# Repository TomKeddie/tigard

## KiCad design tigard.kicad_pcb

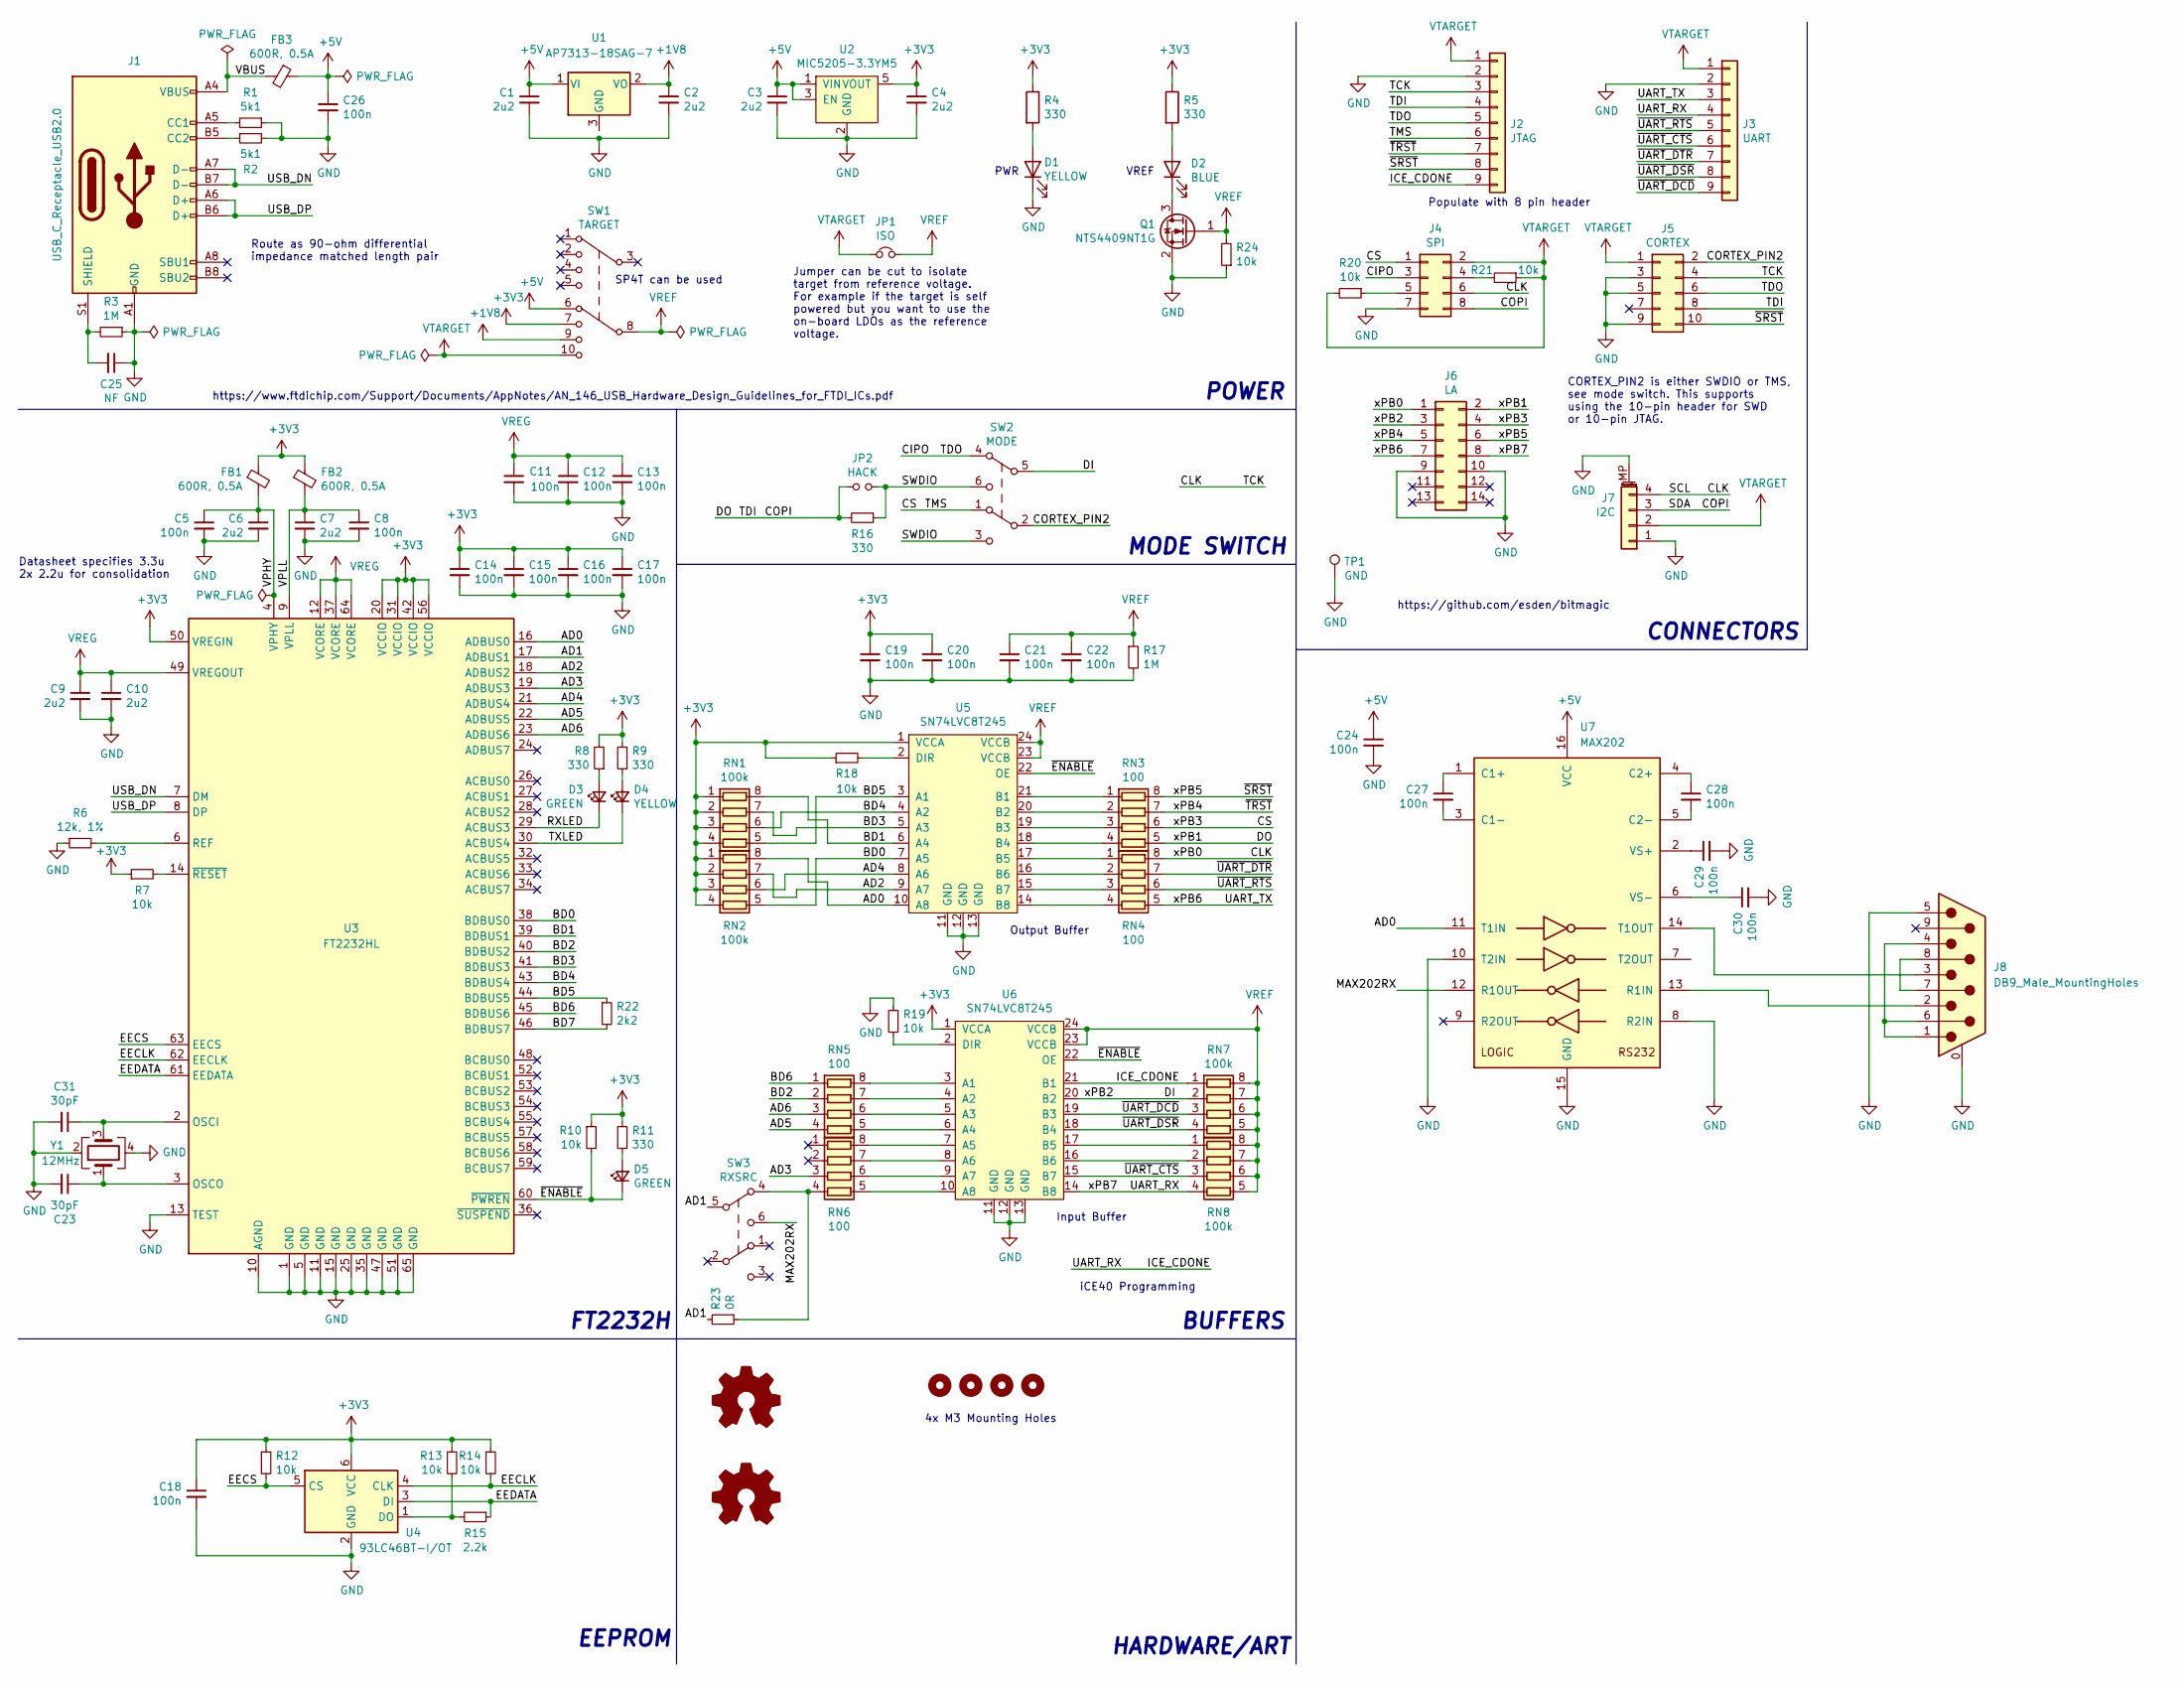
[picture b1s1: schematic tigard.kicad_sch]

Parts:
C1, C2, C3, C4, C6, C7, C9, C10: 2u2; C_0805_2012Metric; LCSC C307419
C5, C8, C11, C12, C13, C14, C15, C16, C17, C18, C19, C20, C21, C22, C24, C26, C27, C28, C29, C30: 100n; C_0805_2012Metric; LCSC C100072
C23, C31: 30pF; C_0805_2012Metric; LCSC C159804
C25: NF; C_0805_2012Metric
D1, D4: YELLOW; LED_0805_2012Metric; LCSC C160477
D2: BLUE; LED_0805_2012Metric; LCSC C157738
D3, D5: GREEN; LED_0805_2012Metric; LCSC C12065
FB1, FB2, FB3: 600R, 0.5A; L_0805_2012Metric; LCSC C76886
H1, H2, H3, H4: MountingHole; MountingHole_3.2mm_M3_ISO7380
J1: USB_C_Receptacle_USB2.0; USB_C_Receptacle_HRO_TYPE-C-31-M-12; LCSC C165948
J2: JTAG; PinHeader_1x09_P2.54mm_Vertical; LCSC C358689
J3: UART; PinHeader_1x09_P2.54mm_Vertical; LCSC C492408
J4: SPI; PinHeader_2x04_P2.54mm_Vertical; LCSC C358693
J5: CORTEX; PinHeader_2x05_P1.27mm_Vertical_SMD; LCSC C448647
J6: LA; PinHeader_2x07_P1.27mm_Vertical_SMD
J7: I2C; JST_SH_SM04B-SRSS-TB_1x04-1MP_P1.00mm_Horizontal; LCSC C160404
J8: DB9_Male_MountingHoles; DSUB-9_Male_Horizontal_P2.77x2.84mm_EdgePinOffset7.70mm_Hou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
JP1: ISO; SolderJumper-2_P1.3mm_Bridged_RoundedPad1.0x1.5mm
JP2: HACK; SolderJumper-2_P1.3mm_Open_RoundedPad1.0x1.5mm
LOGO1: Logo_Open_Hardware_Small; OSHW-Symbol_4.4x4mm_SilkScreen
LOGO2: Logo_Open_Hardware_Small; Tigard_Logo
Q1: NTS4409NT1G; SOT-323_SC-70; LCSC C88711
R1, R2: 5k1; L_0805_2012Metric; LCSC C25941
R3, R17: 1M; L_0805_2012Metric; LCSC C26087
R4, R5, R8, R9, R11, R16: 330; L_0805_2012Metric; LCSC C25104
R6: 12k, 1%; L_0805_2012Metric; LCSC C25752
R7, R10, R12, R13, R14, R18, R19, R20, R21, R24: 10k; L_0805_2012Metric; LCSC C301923
R15: 2.2k; L_0805_2012Metric; LCSC C25879
R22: 2k2; L_0805_2012Metric; LCSC C25933
R23: 0R; L_0805_2012Metric; LCSC C25104
RN1, RN2, RN7, RN8: 100k; R_Array_Convex_4x0603; LCSC C25724
RN3, RN4, RN5, RN6: 100; R_Array_Convex_4x0603; LCSC C48442
SW1: TARGET; SW_ALPS_SSSS224100_DP4T; LCSC C255514
SW2: MODE; SW_CuK_JS202011CQN_DPDT_Straight; LCSC C221663
SW3: RXSRC; SW_CuK_JS202011CQN_DPDT_Straight; LCSC C221663
TP1: GND; TestPoint_Keystone_5000-5004_Miniature; LCSC C238122
U1: AP7313-18SAG-7; SOT-23_RoundRect
U2: MIC5205-3.3YM5; SOT-23-5_RoundRect; LCSC C150742
U3: FT2232HL; LQFP-64_10x10mm_P0.5mm; LCSC C193662
U4: 93LC46BT-I/OT; SOT-23-6_RoundRect; LCSC C190271
U5, U6: SN74LVC8T245; SOIC-24W_7.5x15.4mm_P1.27mm; LCSC C27643
U7: MAX202; SOIC-16_3.9x9.9mm_P1.27mm
Y1: 12MHz; Crystal_SMD_3225-4Pin_3.2x2.5mm_RoundRect; LCSC C9002

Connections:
+1V8: C2.1, SW1.9, U1.2 (VO)
+3V3: C4.1, C14.1, C15.1, C16.1, C17.1, C18.1, C19.1, C20.1, FB1.1, FB2.1, R4.1, R5.1, R7.1, R8.2, R9.2, R10.1, R11.2, R12.1, R13.1, R14.1, R18.1, RN1.1 (R1.1), RN1.2 (R2.1), RN1.3 (R3.1), RN1.4 (R4.1), RN2.1 (R1.1), RN2.2 (R2.1), RN2.3 (R3.1), RN2.4 (R4.1), SW1.7, U2.5 (VOUT), U3.20 (VCCIO), U3.31 (VCCIO), U3.42 (VCCIO), U3.50 (VREGIN), U3.56 (VCCIO), U4.6 (VCC), U5.1 (VCCA), U6.1 (VCCA)
+5V: C1.1, C3.1, C24.1, C26.1, FB3.1, SW1.6, U1.1 (VI), U2.1 (VIN), U2.3 (EN), U7.16 (VCC)
/AD0: RN2.8 (R1.2), U3.16 (ADBUS0), U5.10 (A8), U7.11 (T1IN)
/AD1: R23.2, SW3.5, U3.17 (ADBUS1)
/AD2: RN2.7 (R2.2), U3.18 (ADBUS2), U5.9 (A7)
/AD3: RN6.3 (R3.1), U3.19 (ADBUS3)
/AD4: RN2.6 (R3.2), U3.21 (ADBUS4), U5.8 (A6)
/AD5: RN5.4 (R4.1), U3.22 (ADBUS5)
/AD6: RN5.3 (R3.1), U3.23 (ADBUS6)
/BD0: RN2.5 (R4.2), U3.38 (BDBUS0), U5.7 (A5)
/BD1: RN1.8 (R1.2), U3.39 (BDBUS1), U5.6 (A4)
/BD2: RN5.2 (R2.1), U3.40 (BDBUS2)
/BD3: RN1.7 (R2.2), U3.41 (BDBUS3), U5.5 (A3)
/BD4: RN1.6 (R3.2), U3.43 (BDBUS4), U5.4 (A2)
/BD5: R22.1, RN1.5 (R4.2), U3.44 (BDBUS5), U5.3 (A1)
/BD6: RN5.1 (R1.1), U3.45 (BDBUS6)
/BD7: R22.2, U3.46 (BDBUS7)
/CIPO: J2.5, J4.3, J5.6, SW2.4
/CLK: J2.3, J4.6, J5.4, J6.1, J7.4, RN4.8 (R1.2)
/COPI: J2.4, J4.8, J5.8, J6.2, J7.3, JP2.1, R16.2, RN3.5 (R4.2)
/CORTEX_PIN2: J5.2, SW2.2
/CS: J2.6, J4.1, J6.4, RN3.6 (R3.2), SW2.1
/DI: J6.3, RN7.2 (R2.1), SW2.5, U6.20 (B2)
/EECLK: R14.2, U3.62 (EECLK), U4.4 (CLK)
/EECS: R12.2, U3.63 (EECS), U4.5 (CS)
/EEDATA: R15.1, U3.61 (EEDATA), U4.3 (DI)
/ICE_CDONE: J2.9, J3.4, J6.8, RN7.1 (R1.1), RN8.4 (R4.1), U6.14 (B8), U6.21 (B1)
/MAX202RX: SW3.6, U7.12 (R1OUT)
/RXLED: D3.1 (K), U3.29 (ACBUS3)
/SWDIO: JP2.2, R16.1, SW2.3, SW2.6
/TXLED: D4.1 (K), U3.30 (ACBUS4)
/UART_TX: J3.3, J6.7, RN4.5 (R4.2)
/USB_DN: J1.A7 (D-), J1.B7 (D-), U3.7 (DM)
/USB_DP: J1.A6 (D+), J1.B6 (D+), U3.8 (DP)
/VBUS: FB3.2, J1.A4 (VBUS), J1.A9 (VBUS), J1.B4 (VBUS), J1.B9 (VBUS)
/VPHY: C5.1, C6.1, FB1.2, U3.4 (VPHY)
/VPLL: C7.1, C8.1, FB2.2, U3.9 (VPLL)
/xPB4: J2.7, J6.5, RN3.7 (R2.2)
/xPB5: J2.8, J5.10, J6.6, RN3.8 (R1.2)
/~ENABLE: D5.1 (K), R10.2, U3.60 (~PWREN), U5.22 (OE), U6.22 (OE)
/~UART_CTS: J3.6, RN8.3 (R3.1), U6.15 (B7)
/~UART_DCD: J3.9, RN7.3 (R3.1), U6.19 (B3)
/~UART_DSR: J3.8, RN7.4 (R4.1), U6.18 (B4)
/~UART_DTR: J3.7, RN4.7 (R2.2)
/~UART_RTS: J3.5, RN4.6 (R3.2)
GND: C1.2, C2.2, C3.2, C4.2, C5.2, C6.2, C7.2, C8.2, C9.2, C10.2, C11.2, C12.2, C13.2, C14.2, C15.2, C16.2, C17.2, C18.2, C19.2, C20.2, C21.2, C22.2, C23.2, C24.2, C25.1, C26.2, C29.2, C30.2, C31.2, D1.1 (K), J1.A1 (GND), J1.A12 (GND), J1.B1 (GND), J1.B12 (GND), J2.2, J3.2, J4.7, J5.3, J5.5, J5.9, J6.9, J6.10, J7.1, J7.MP (MountPin), J8.0 (PAD), J8.5, Q1.2 (S), R1.1, R2.2, R3.1, R6.1, R17.2, R19.2, R24.1, TP1.1, U2.2 (GND), U3.1 (GND), U3.5 (GND), U3.10 (AGND), U3.11 (GND), U3.13 (TEST), U3.15 (GND), U3.25 (GND), U3.35 (GND), U3.47 (GND), U3.51 (GND), U3.65 (GND), U4.2 (GND), U5.11 (GND), U5.12 (GND), U5.13 (GND), U6.11 (GND), U6.12 (GND), U6.13 (GND), U7.8 (R2IN), U7.10 (T2IN), U7.15 (GND), Y1.2, Y1.4
unnamed: C25.2, J1.S1 (SHIELD), R3.2
unnamed: C27.1, U7.1 (C1+)
unnamed: C27.2, U7.3 (C1-)
unnamed: C28.1, U7.4 (C2+)
unnamed: C28.2, U7.5 (C2-)
unnamed: C29.1, U7.2 (VS+)
unnamed: C30.1, U7.6 (VS-)
unnamed: D1.2 (A), R4.2
unnamed: D2.1 (K), Q1.3 (D)
unnamed: D2.2 (A), R5.2
unnamed: D3.2 (A), R8.1
unnamed: D4.2 (A), R9.1
unnamed: D5.2 (A), R11.1
unnamed: J1.A5 (CC1), R1.2
unnamed: J1.B5 (CC2), R2.1
unnamed: J4.4, R21.2
unnamed: J4.5, R20.1
unnamed: J8.1, J8.4, J8.6
unnamed: J8.2, U7.13 (R1IN)
unnamed: J8.3, U7.14 (T1OUT)
unnamed: J8.7, J8.8
unnamed: R6.2, U3.6 (REF)
unnamed: R7.2, U3.14 (~RESET)
unnamed: R13.2, R15.2, U4.1 (DO)
unnamed: R18.2, U5.2 (DIR)
unnamed: R19.1, U6.2 (DIR)
unnamed: R23.1, RN6.4 (R4.1), SW3.4
unnamed: RN3.1 (R1.1), U5.21 (B1)
unnamed: RN3.2 (R2.1), U5.20 (B2)
unnamed: RN3.3 (R3.1), U5.19 (B3)
unnamed: RN3.4 (R4.1), U5.18 (B4)
unnamed: RN4.1 (R1.1), U5.17 (B5)
unnamed: RN4.2 (R2.1), U5.16 (B6)
unnamed: RN4.3 (R3.1), U5.15 (B7)
unnamed: RN4.4 (R4.1), U5.14 (B8)
unnamed: RN5.5 (R4.2), U6.6 (A4)
unnamed: RN5.6 (R3.2), U6.5 (A3)
unnamed: RN5.7 (R2.2), U6.4 (A2)
unnamed: RN5.8 (R1.2), U6.3 (A1)
unnamed: RN6.5 (R4.2), U6.10 (A8)
unnamed: RN6.6 (R3.2), U6.9 (A7)
unnamed: RN6.7 (R2.2), U6.8 (A6)
unnamed: RN6.8 (R1.2), U6.7 (A5)
unnamed: RN8.1 (R1.1), U6.17 (B5)
unnamed: RN8.2 (R2.1), U6.16 (B6)
unnamed: C31.1, U3.2 (OSCI), Y1.3
unnamed: C23.1, U3.3 (OSCO), Y1.1
VREF: C21.1, C22.1, JP1.2, Q1.1 (G), R17.1, R24.2, RN7.5 (R4.2), RN7.6 (R3.2), RN7.7 (R2.2), RN7.8 (R1.2), RN8.5 (R4.2), RN8.6 (R3.2), RN8.7 (R2.2), RN8.8 (R1.2), SW1.8, U5.23 (VCCB), U5.24 (VCCB), U6.23 (VCCB), U6.24 (VCCB)
VREG: C9.1, C10.1, C11.1, C12.1, C13.1, U3.12 (VCORE), U3.37 (VCORE), U3.49 (VREGOUT), U3.64 (VCORE)
VTARGET: J2.1, J3.1, J4.2, J5.1, J7.2, JP1.1, R20.2, R21.1, SW1.10

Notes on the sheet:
Input Buffer
MODE SWITCH
CORTEX_PIN2 is either SWDIO or TMS, see mode switch. This supports using the 10-pin header for SWD or 10-pin JTAG.
https://www.ftdichip.com/Support/Documents/AppNotes/AN_146_USB_Hardware_Design_Guidelines_for_FTDI_ICs.pdf
BUFFERS
EEPROM
https://github.com/esden/bitmagic
PWR
CONNECTORS
Output Buffer
Route as 90-ohm differential impedance matched length pair
SP4T can be used
HARDWARE/ART
Populate with 8 pin header
iCE40 Programming
Datasheet specifies 3.3u 2x 2.2u for consolidation
POWER
4x M3 Mounting Holes
FT2232H
VREF
Jumper can be cut to isolate target from reference voltage. For example if the target is self powered but you want to use the on-board LDOs as the reference voltage.

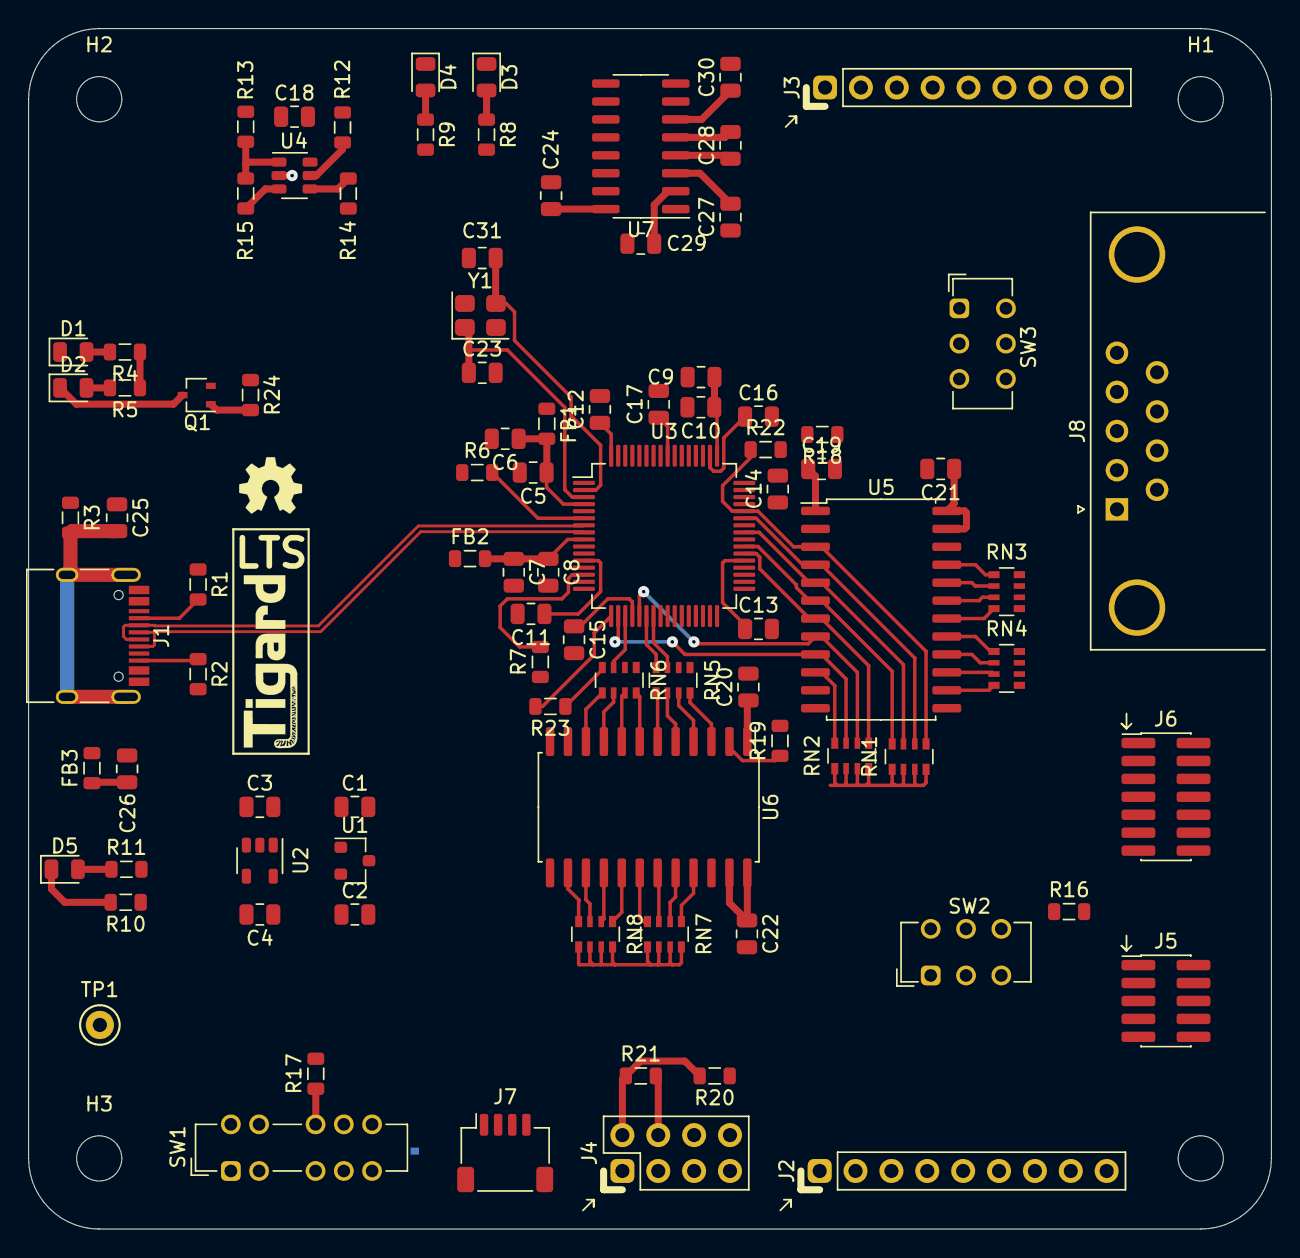
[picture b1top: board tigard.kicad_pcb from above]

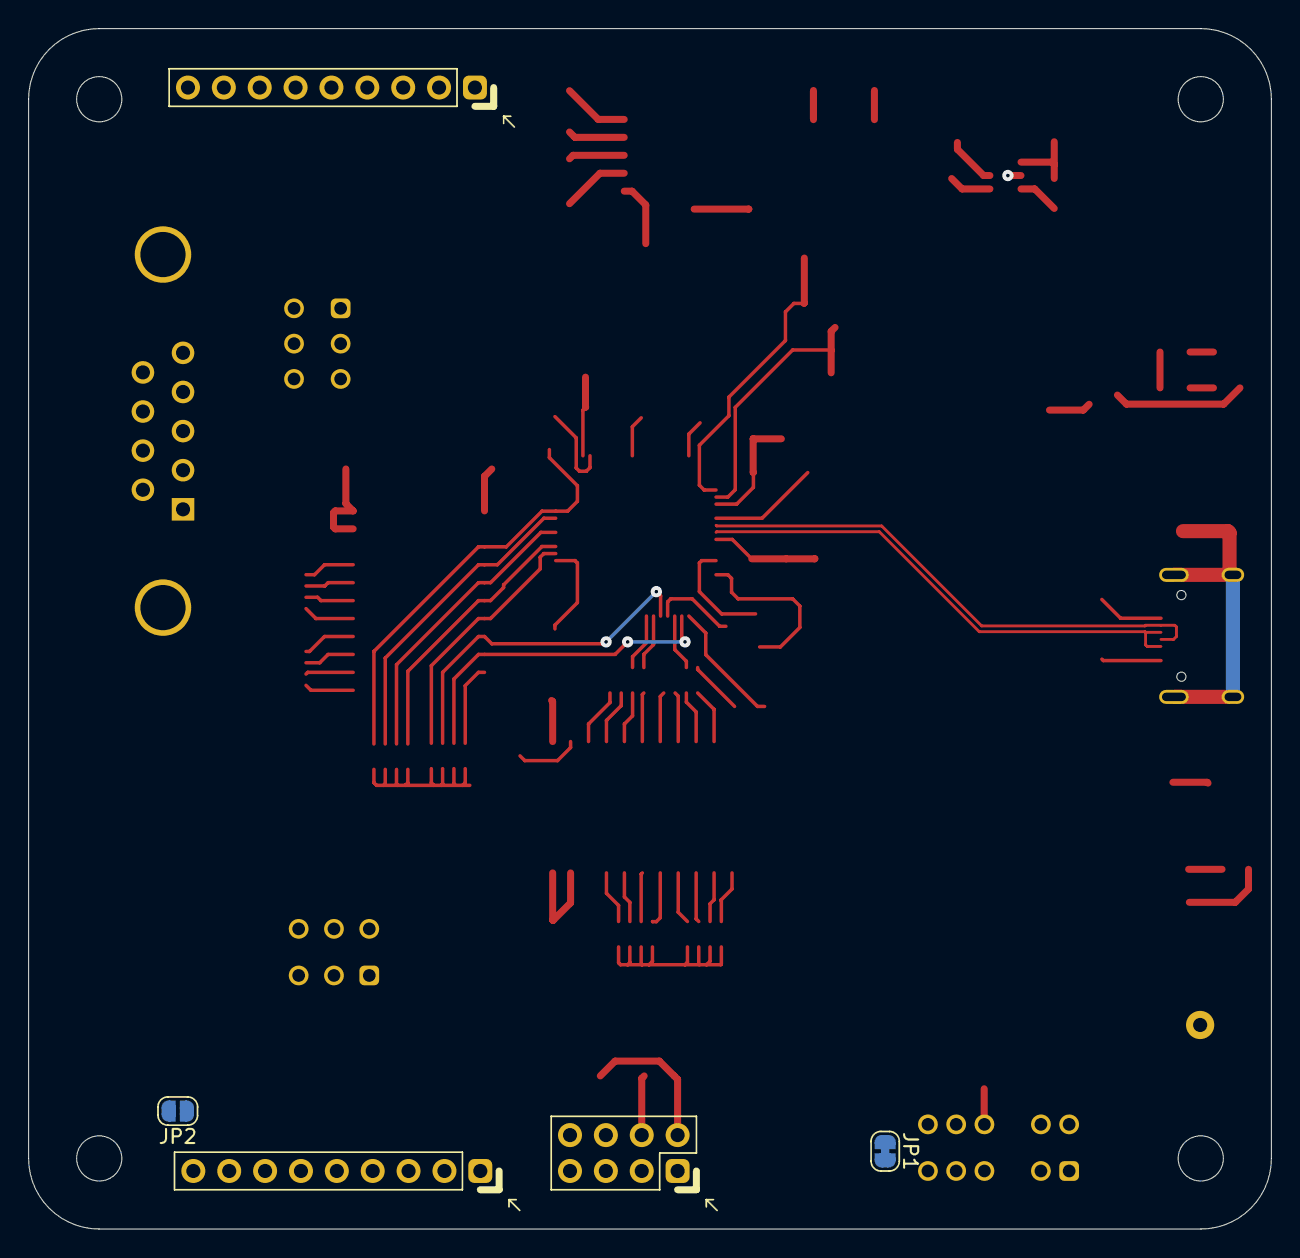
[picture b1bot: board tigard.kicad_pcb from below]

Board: 2 copper layers, 88.0 x 85.0 mm, 100 parts (2 on the bottom side), 97 nets.

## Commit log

2022-09-12 tigard-lts: update to kicad 6, remove pcb
2022-09-12 tigard-lts: first pass at placement
2022-09-13 tomk-tigard-lts: progress commit - board outline
2022-09-16 tigard-lts: progress commit
2022-09-16 tomk-tigard-lts: progress commit

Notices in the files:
tigard.kicad_sch:
Copyright 2020 Franklin Harding
Licensed under CC-BY-SA 4.0
